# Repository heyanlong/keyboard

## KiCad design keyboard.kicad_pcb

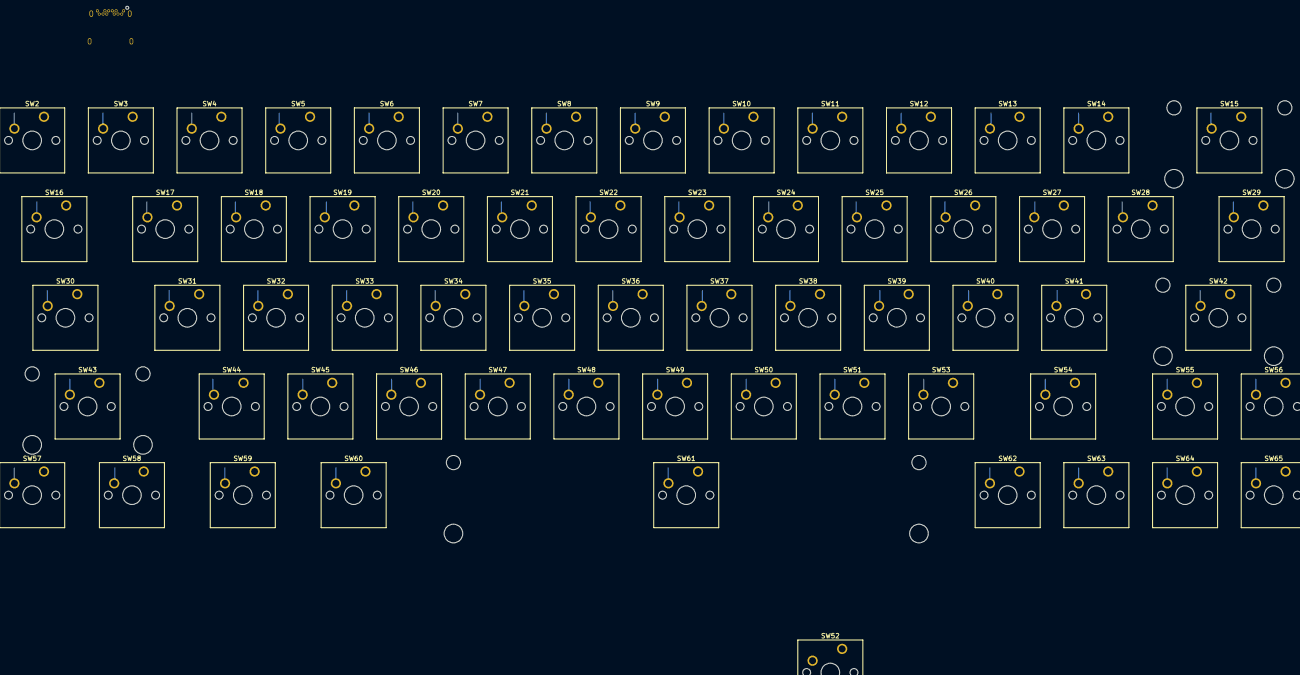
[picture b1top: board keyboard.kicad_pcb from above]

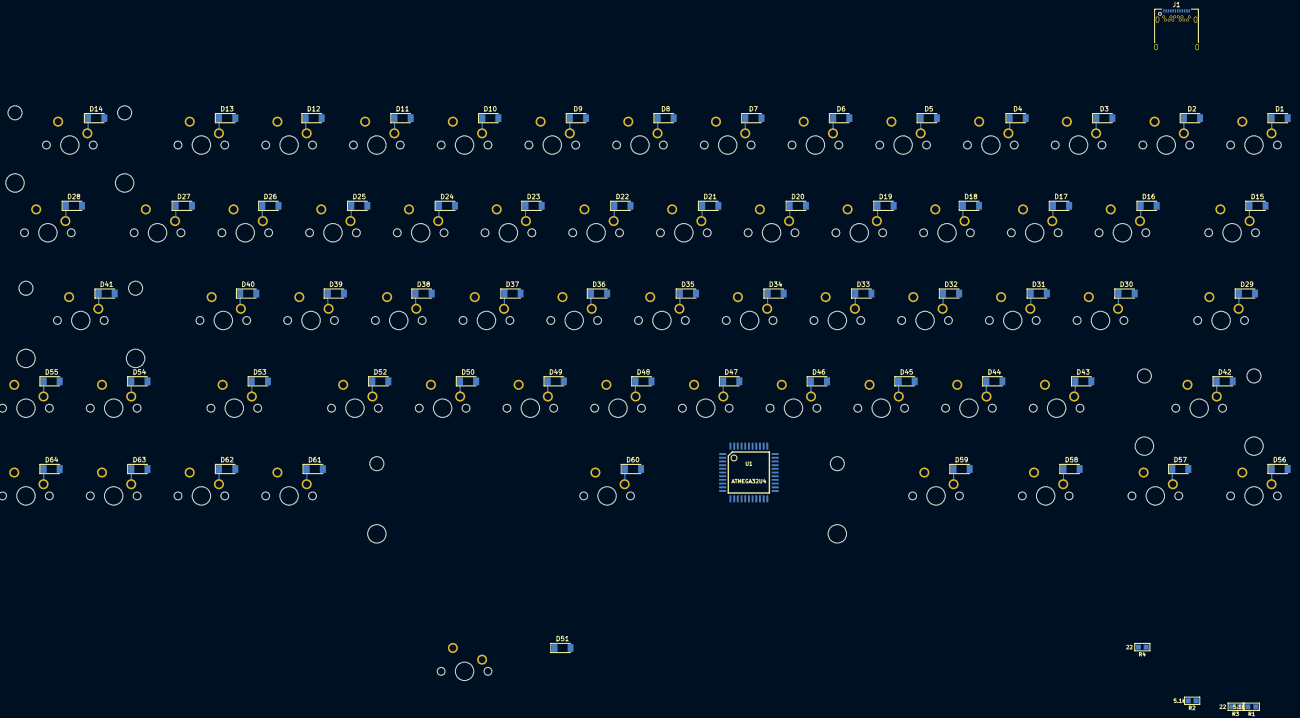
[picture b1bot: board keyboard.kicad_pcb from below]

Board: 2 copper layers, 134 parts (70 on the bottom side), 92 nets.

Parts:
D1, D2, D3, D4, D5, D6, D7, D8, D9, D10, D11, D12, D13, D14, D15, D16, D17, D18, D19, D20, D21, D22, D23, D24, D25, D26, D27, D28, D29, D30, D31, D32, D33, D34, D35, D36, D37, D38, D39, D40, D41, D42, D43, D44, D45, D46, D47, D48, D49, D50, D51, D52, D53, D54, D55, D56, D57, D58, D59, D60, D61, D62, D63, D64: D; D_MiniMELF
J1: USB_C_Receptacle; USB_C_Receptacle_Amphenol_12401548E4-2A
R1, R2: 5.1k; R_1608
R3, R4: 22; R_1608
SW2: ESC; SW_Cherry_MX1A_1.00u_PCB
SW3: 1; SW_Cherry_MX1A_1.00u_PCB
SW4: 2; SW_Cherry_MX1A_1.00u_PCB
SW5: 3; SW_Cherry_MX1A_1.00u_PCB
SW6: 4; SW_Cherry_MX1A_1.00u_PCB
SW7: 5; SW_Cherry_MX1A_1.00u_PCB
SW8: 6; SW_Cherry_MX1A_1.00u_PCB
SW9: 7; SW_Cherry_MX1A_1.00u_PCB
SW10: 8; SW_Cherry_MX1A_1.00u_PCB
SW11: 9; SW_Cherry_MX1A_1.00u_PCB
SW12: 0; SW_Cherry_MX1A_1.00u_PCB
SW13: -; SW_Cherry_MX1A_1.00u_PCB
SW14: =; SW_Cherry_MX1A_1.00u_PCB
SW15: delete; SW_Cherry_MX1A_2.00u_PCB
SW16: tab; SW_Cherry_MX1A_1.50u_PCB
SW17: q; SW_Cherry_MX1A_1.00u_PCB
SW18: w; SW_Cherry_MX1A_1.00u_PCB
SW19: e; SW_Cherry_MX1A_1.00u_PCB
SW20: r; SW_Cherry_MX1A_1.00u_PCB
SW21: t; SW_Cherry_MX1A_1.00u_PCB
SW22: y; SW_Cherry_MX1A_1.00u_PCB
SW23: u; SW_Cherry_MX1A_1.00u_PCB
SW24: i; SW_Cherry_MX1A_1.00u_PCB
SW25: o; SW_Cherry_MX1A_1.00u_PCB
SW26: p; SW_Cherry_MX1A_1.00u_PCB
SW27: [; SW_Cherry_MX1A_1.00u_PCB
SW28: ]; SW_Cherry_MX1A_1.00u_PCB
SW29: \; SW_Cherry_MX1A_1.50u_PCB
SW30: lock; SW_Cherry_MX1A_1.75u_PCB
SW31: a; SW_Cherry_MX1A_1.00u_PCB
SW32: s; SW_Cherry_MX1A_1.00u_PCB
SW33: d; SW_Cherry_MX1A_1.00u_PCB
SW34: f; SW_Cherry_MX1A_1.00u_PCB
SW35: g; SW_Cherry_MX1A_1.00u_PCB
SW36: h; SW_Cherry_MX1A_1.00u_PCB
SW37: j; SW_Cherry_MX1A_1.00u_PCB
SW38: k; SW_Cherry_MX1A_1.00u_PCB
SW39: l; SW_Cherry_MX1A_1.00u_PCB
SW40: ;; SW_Cherry_MX1A_1.00u_PCB
SW41: '; SW_Cherry_MX1A_1.00u_PCB
SW42: return; SW_Cherry_MX1A_2.25u_PCB
SW43: shift; SW_Cherry_MX1A_2.25u_PCB
SW44: z; SW_Cherry_MX1A_1.00u_PCB
SW45: x; SW_Cherry_MX1A_1.00u_PCB
SW46: c; SW_Cherry_MX1A_1.00u_PCB
SW47: v; SW_Cherry_MX1A_1.00u_PCB
SW48: b; SW_Cherry_MX1A_1.00u_PCB
SW49: n; SW_Cherry_MX1A_1.00u_PCB
SW50: m; SW_Cherry_MX1A_1.00u_PCB
SW51: ,; SW_Cherry_MX1A_1.00u_PCB
SW52: .; SW_Cherry_MX1A_1.00u_PCB
SW53: /; SW_Cherry_MX1A_1.00u_PCB
SW54: shift; SW_Cherry_MX1A_1.75u_PCB
SW55: up; SW_Cherry_MX1A_1.00u_PCB
SW56: delete; SW_Cherry_MX1A_1.00u_PCB
SW57: fn; SW_Cherry_MX1A_1.00u_PCB
SW58: control; SW_Cherry_MX1A_1.25u_PCB
SW59: option; SW_Cherry_MX1A_1.25u_PCB
SW60: command; SW_Cherry_MX1A_1.25u_PCB
SW61: space; SW_Cherry_MX1A_6.25u_PCB
SW62: command; SW_Cherry_MX1A_1.00u_PCB
SW63: left; SW_Cherry_MX1A_1.00u_PCB
SW64: down; SW_Cherry_MX1A_1.00u_PCB
SW65: right; SW_Cherry_MX1A_1.00u_PCB
U1: ATMEGA32U4; QFP44

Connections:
+5V: U1.14, U1.24, U1.34, U1.44
/key/col1: D1.2, D15.2, D29.2, D42.2, D56.2
/key/col2: D2.2, D16.2, D30.2, D43.2, D57.2
/key/col3: D3.2, D17.2, D31.2, D44.2, D58.2
/key/col4: D4.2, D18.2, D32.2, D45.2, D59.2
/key/col5: D5.2, D19.2, D33.2, D46.2, D60.2
/key/col6: D6.2, D20.2, D34.2, D47.2, D61.2
/key/col7: D7.2, D21.2, D35.2, D48.2
/key/col8: D8.2, D22.2, D36.2, D49.2
/key/col9: D9.2, D23.2, D37.2, D50.2
/key/col10: D10.2, D24.2, D38.2, D51.2
/key/col11: D11.2, D25.2, D39.2, D52.2
/key/col12: D12.2, D26.2, D40.2, D53.2, D62.2
/key/col13: D13.2, D27.2, D41.2, D54.2, D63.2
/key/col14: D14.2, D28.2, D55.2, D64.2
GND: J1.A1, J1.A12, J1.B1, J1.B12, J1.S1, R1.1, R2.1, U1.5, U1.15, U1.23, U1.35, U1.43
unnamed: D1.1, SW2.2
unnamed: D2.1, SW3.2
unnamed: D3.1, SW4.2
unnamed: D4.1, SW5.2
unnamed: D5.1, SW6.2
unnamed: D6.1, SW7.2
unnamed: D7.1, SW8.2
unnamed: D8.1, SW9.2
unnamed: D9.1, SW10.2
unnamed: D10.1, SW11.2
unnamed: D11.1, SW12.2
unnamed: D12.1, SW13.2
unnamed: D13.1, SW14.2
unnamed: D14.1, SW15.2
unnamed: D15.1, SW16.2
unnamed: D16.1, SW17.2
unnamed: D17.1, SW18.2
unnamed: D18.1, SW19.2
unnamed: D19.1, SW20.2
unnamed: D20.1, SW21.2
unnamed: D21.1, SW22.2
unnamed: D22.1, SW23.2
unnamed: D23.1, SW24.2
unnamed: D24.1, SW25.2
unnamed: D25.1, SW26.2
unnamed: D26.1, SW27.2
unnamed: D27.1, SW28.2
unnamed: D28.1, SW29.2
unnamed: D29.1, SW30.2
unnamed: D30.1, SW31.2
unnamed: D31.1, SW32.2
unnamed: D32.1, SW33.2
unnamed: D33.1, SW34.2
unnamed: D34.1, SW35.2
unnamed: D35.1, SW36.2
unnamed: D36.1, SW37.2
unnamed: D37.1, SW38.2
unnamed: D38.1, SW39.2
unnamed: D39.1, SW40.2
unnamed: D40.1, SW41.2
unnamed: D41.1, SW42.2
unnamed: D42.1, SW43.2
unnamed: D43.1, SW44.2
unnamed: D44.1, SW45.2
unnamed: D45.1, SW46.2
unnamed: D46.1, SW47.2
unnamed: D47.1, SW48.2
unnamed: D48.1, SW49.2
unnamed: D49.1, SW50.2
unnamed: D50.1, SW51.2
unnamed: D51.1, SW52.2
unnamed: D52.1, SW53.2
unnamed: D53.1, SW54.2
unnamed: D54.1, SW55.2
unnamed: D55.1, SW56.2
unnamed: D56.1, SW57.2
unnamed: D57.1, SW58.2
unnamed: D58.1, SW59.2
unnamed: D59.1, SW60.2
unnamed: D60.1, SW61.2
unnamed: D61.1, SW62.2
unnamed: D62.1, SW63.2
unnamed: D63.1, SW64.2
unnamed: D64.1, SW65.2
unnamed: J1.A5, R1.2
unnamed: J1.A6, J1.B6, R4.2
unnamed: J1.A7, J1.B7, R3.2
unnamed: J1.B5, R2.2
unnamed: R3.1, U1.3
unnamed: R4.1, U1.4
ROW0: SW2.1, SW3.1, SW4.1, SW5.1, SW6.1, SW7.1, SW8.1, SW9.1, SW10.1, SW11.1, SW12.1, SW13.1, SW14.1, SW15.1, U1.8
ROW1: SW16.1, SW17.1, SW18.1, SW19.1, SW20.1, SW21.1, SW22.1, SW23.1, SW24.1, SW25.1, SW26.1, SW27.1, SW28.1, SW29.1, U1.9
ROW2: SW30.1, SW31.1, SW32.1, SW33.1, SW34.1, SW35.1, SW36.1, SW37.1, SW38.1, SW39.1, SW40.1, SW41.1, SW42.1, U1.10
ROW3: SW43.1, SW44.1, SW45.1, SW46.1, SW47.1, SW48.1, SW49.1, SW50.1, SW51.1, SW52.1, SW53.1, SW54.1, SW55.1, SW56.1, U1.11
ROW4: SW57.1, SW58.1, SW59.1, SW60.1, SW61.1, SW62.1, SW63.1, SW64.1, SW65.1, U1.28
VUSB: J1.A4, J1.A9, J1.B4, J1.B9, U1.2, U1.7

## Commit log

2018-10-08 usb OK👏
2018-10-08 add library
2018-10-10 update micro system
2018-10-12 matrix layout
2018-10-15 layout
2018-10-15 pcb layout
2018-10-16 layout pcb
2018-10-24 change layout
